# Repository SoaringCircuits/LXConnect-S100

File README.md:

# LXConnect S100

## General remarks
This small board is designed to simplify and organize the wiring in your glider.
It provides a clean extension point to wire the cables for the LX S100 standalone variometer, reducing clunky connectors hanging free.

## Electrical installation
Installation is easy, but some basic skills in creating cable harnesses are needed to create the connection from S100 to the board.
While the S100 uses a D-Sub-15, the board uses a D-SUB-15HD to save space.
The following diagram shows the harness to build to connect S100 and board. 

The board provides terminals for power, the switching inputs (SC, VP, IN1-4, OAT), as well as a connector for the CAN-Bus with optional terminator directly on the board.

## D-SUB Connectors
The board uses two D-SUB connectors, one for the connection to the S100 and one for the CAN-Bus.
I recommend to use connectors with crimped contacts for both connectors, but solderd ones will work as well.
All connections are direct lines, there is no need to crimp/solder more than one cable to a single contact.

### Connector to S100
To connect the board to the S100, a cable with a male D-SUB-15 High-Density (board) and a female D-SUB 15 (S100) is used.
If using a shielded cable, a conductive backshell with the shielding clamped by the strain releif will connect the shielding to ground.

On the board side (D-SUB 15HD male), the connector has the following pin distribution:

| **PIN** | **Name**     | **Function**                |
|---------|--------------|-----------------------------|
| 1       | IN1          | External input 1            |
| 2       | GND          | Ground                      |
| 3       | GND          | Ground                      |
| 4       | nc           | not connected               |
| 5       | 12V-IN       | 12V Power to S100           |
| 6       | IN2          | External input 2            |
| 7       | IN4          | External input 4            |
| 8       | nc           | not connected               |
| 9       | VP           | Vario Priority              |
| 10      | OAT          | Outside Air Temperature     |
| 11      | IN3          | External Input 3            |
| 12      | CAN-Low      | CAN Low                     |
| 13      | CAN-High     | CAN High                    |
| 14      | 12V-OUT      | 12V to external CAN-Devices |
| 15      | SC           | Speed Command switch        |

The numbers on both sides (male and female) are matching, so that pin 1 of the male connector matches with pin 1 of the female side.
Just follow the numbers, they should be printed on the connector!

For the distribution on the S100 side, please see the manual for the LX S100.

## CAN-Bus and terminator
The LX S100 provides a CAN-Bus to connect external devices like a remote stick, flap indicator, etc.
The end of the Bus has to be terminated by a 120 Ohm resistor.

Originally LX provides a big D-SUB Connector with such a resistor to be plugged at the end of the bus.

This board provides a resistor with a solder jumper to properly terminate the bus if no external devices are connected, saving space and free hanging cables and connectors.
If the onboard terminator should be used, just close the jumper by soldering it together.

The CAN-Bus connector on the board uses the same pin distribution as the S100 (at the time of writing) on a D-SUB 9:

| **PIN** | **Function** |
|---------|--------------|
| 1       | nv           |
| 2       | CAN-Low      |
| 3       | GND          |
| 4       | nc           |
| 5       | GND          |
| 6       | nc           |
| 7       | CAN-High     |
| 8       | nc           |
| 9       | 12V-OUT      |

## Wago Terminals
All terminals are easy to operate, just push the actuator with a little screwdriver and push-in or pull-out the conductor.

The terminals for fuses and devices are suitable for various types of wires:
- Solid concductor 0.2 - 1.5 mm^2
- Fine-stranded conductor 0.2 - 1.5 mm^2
- Fine-stranded conductor with ferrule 0.25 - 1.0 mm^2

The terminal for the main supply can handle conductors up to:
- Solid concductor 0.1 - 4.0 mm^2
- Fine-stranded conductor 0.1 - 4.0 mm^2
- Fine-stranded conductor with ferrule 0.25 - 2.5 mm^2

## Mechanical installation
The half housing is 3D-printed and reliably protects against short circuits on the contacts on the underside of the board.
With four mounting holes for M3 screws, the board can be securely and firmly mounted in the aircraft, with the screws fixing both the housing and the board at the same time.

## Disclaimer
Installation and use of the board are the sole responsibility of the user.
LXnav, the manufacturer of the S100, is and was NOT involved in the development of the board and can not be hold responsibly for any failures or damage to the device.
The board has been built to the best of my knowledge and belief, but no warranty or guarantee can be given for correct functioning or interference immunity.
The legal usability must be checked before each individual installation and, in case of doubt, clarified with competent and authorized personnel (CFS).

## Licence
Copyright Fabian Schöttler 2025.

This source describes Open Hardware and is licensed under the CERN-OHL-P
v2 or later.

You may redistribute and modify this documentation and make products
using it under the terms of the CERN-OHL-P v2 or later (https:/cern.ch/cern-ohl).
This documentation is distributed WITHOUT ANY EXPRESS OR IMPLIED
WARRANTY, INCLUDING OF MERCHANTABILITY, SATISFACTORY QUALITY
AND FITNESS FOR A PARTICULAR PURPOSE.
Please see the CERN-OHL-P v2 for applicable conditions

## Contact
If you have any questions or suggestions about the board, please send an e-mail to fabian@schoettlerhome.de.

------
Electrical, PCB and case design by [ScotteC](https://github.com/ScotteC)

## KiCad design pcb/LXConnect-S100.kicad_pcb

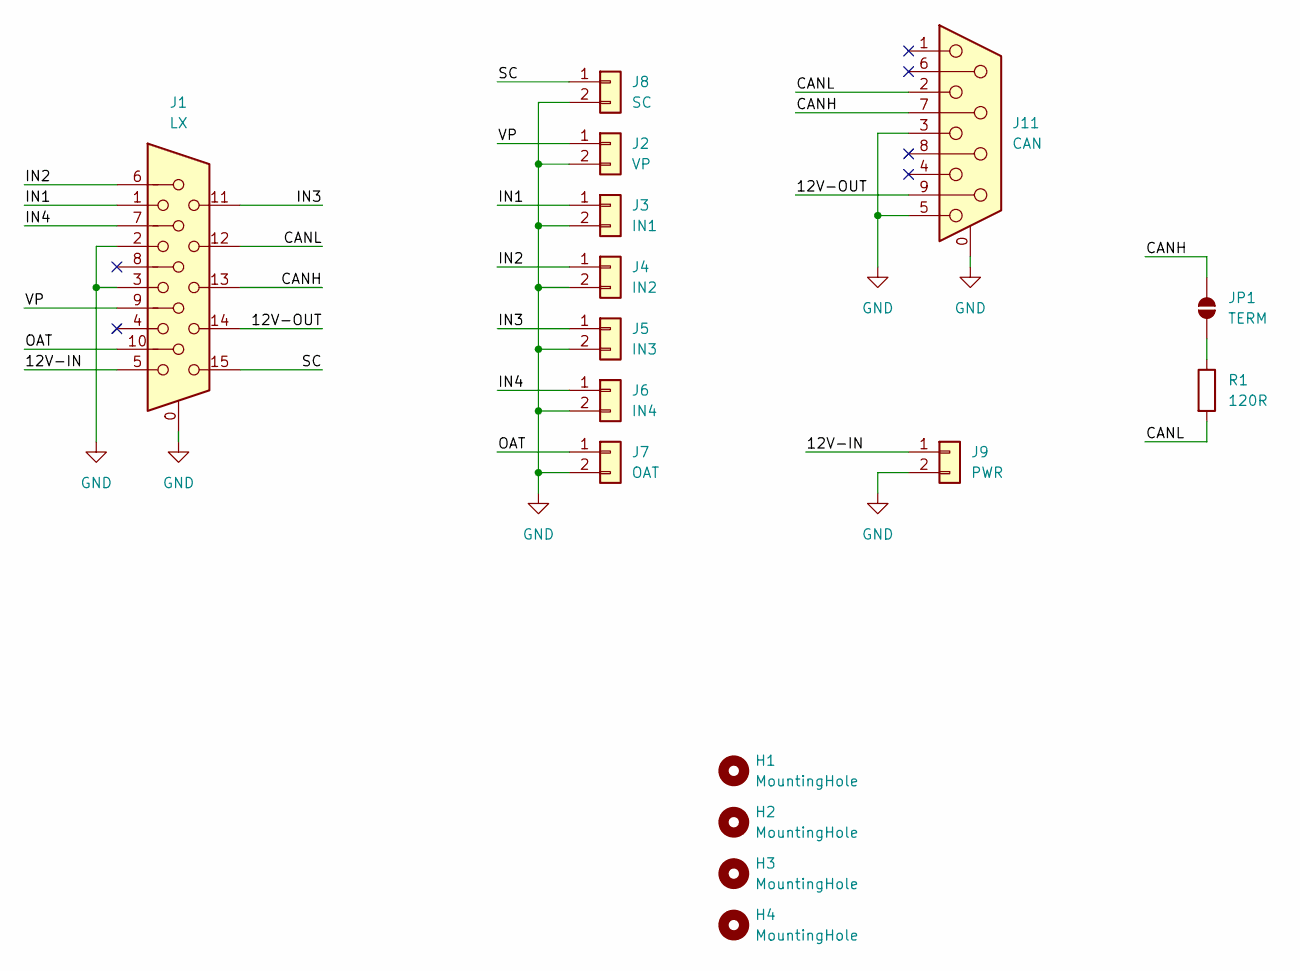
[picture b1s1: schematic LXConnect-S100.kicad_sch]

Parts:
H1, H2, H3, H4: MountingHole; MountingHole_3.2mm_M3
J1: LX; DSUB-15-HD_Socket_Vertical_P2.29x1.98mm_MountingHoles
J2: VP; Wago-250-202
J3: IN1; Wago-250-202
J4: IN2; Wago-250-202
J5: IN3; Wago-250-202
J6: IN4; Wago-250-202
J7: OAT; Wago-250-202
J8: SC; Wago-250-202
J9: PWR; Wago-250-202
J11: CAN; DSUB-9_Socket_Vertical_P2.77x2.84mm_MountingHoles
JP1: TERM; SolderJumper-2_P1.3mm_Open_RoundedPad1.0x1.5mm
R1: 120R; R_0603_1608Metric

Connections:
/12V-IN: J1.5, J9.1
/12V-OUT: J1.14, J11.9
/CANH: J1.13, J11.7, JP1.2 (B)
/CANL: J1.12, J11.2, R1.2
/IN1: J1.1, J3.1
/IN2: J1.6, J4.1
/IN3: J1.11, J5.1
/IN4: J1.7, J6.1
/OAT: J1.10, J7.1
/SC: J1.15, J8.1
/VP: J1.9, J2.1
GND: J1.0, J1.2, J1.3, J2.2, J3.2, J4.2, J5.2, J6.2, J7.2, J8.2, J9.2, J11.0 (PAD), J11.3, J11.5
unnamed: JP1.1 (A), R1.1

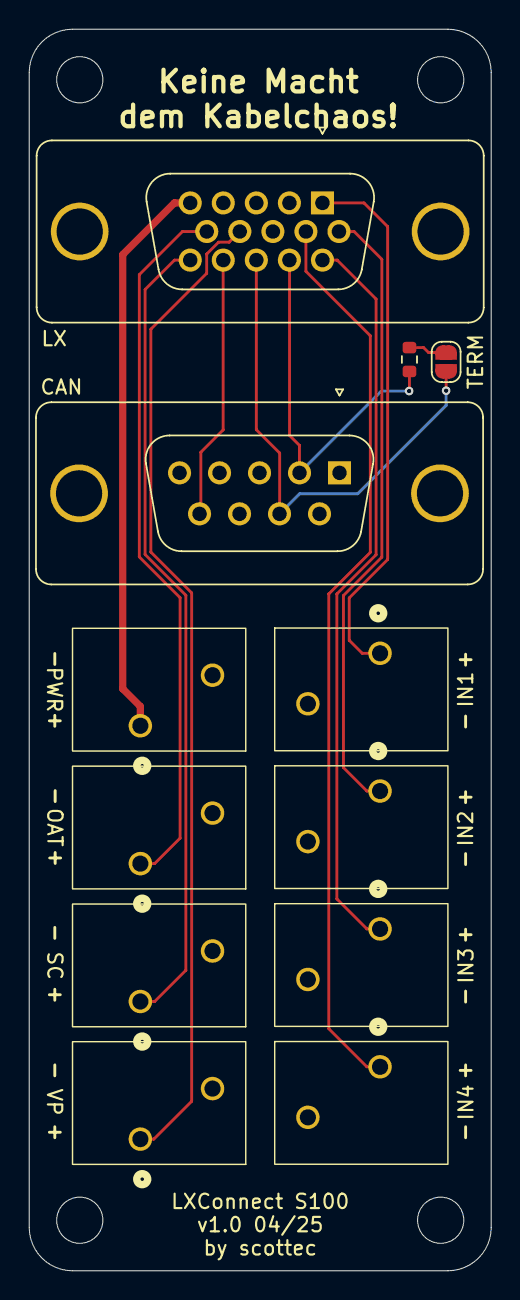
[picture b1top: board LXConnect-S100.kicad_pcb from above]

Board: 2 copper layers, 32.0 x 86.0 mm, 16 parts (0 on the bottom side), 13 nets.

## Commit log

2025-05-02 v1.0
2025-05-02 docu: add board image
2025-05-02 docu
2025-05-02 pcb: docu on board
2025-05-02 docu: update image
2025-05-03 change connector to S100 to socket type to avoid shorts when not plugged
2026-01-11 Enhance README with installation and connector details
    Added detailed connector information and installation instructions for the LXConnect S100 board.
2026-01-11 update picture
2026-01-11 Update README, include number matching for D-SUB
